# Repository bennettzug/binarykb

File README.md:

# binarykb
 
https://www.pcbway.com/project/shareproject/Two_Key_Keyboard.html

CURRENTLY BROKEN; DO NOT ORDER; MAY GET AROUND TO FIXING EVENTUALLY BUT IDK

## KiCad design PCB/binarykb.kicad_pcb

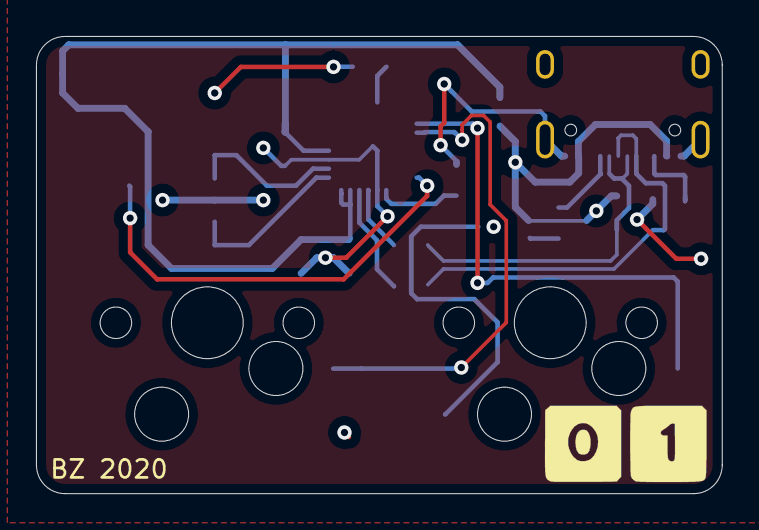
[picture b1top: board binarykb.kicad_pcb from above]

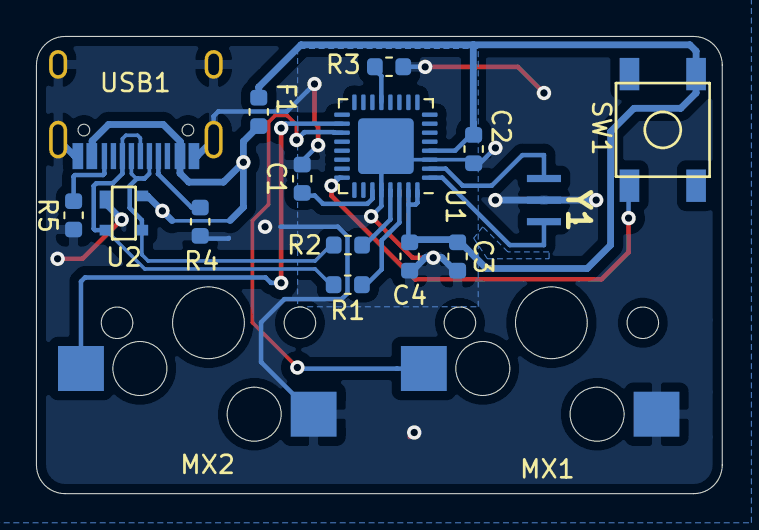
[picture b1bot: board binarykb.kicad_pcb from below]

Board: 2 copper layers, 38.1 x 25.4 mm, 17 parts (15 on the bottom side), 16 nets.

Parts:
C1: 1uF; C_0603_1608Metric
C2, C3: 0.1uF; C_0603_1608Metric
C4: 4.7uF; C_0603_1608Metric
F1: 500mA; Fuse_0603_1608Metric
MX1, MX2: MX-NoLED; MXOnly-1U-Hotswap
R1, R2: 22; R_0603_1608Metric
R3: 10k; R_0603_1608Metric
R4, R5: 5.1k; R_0603_1608Metric
SW1: SW_PUSH; SKQG-1155865
U1: ATmega32U2-MU; QFN-32-1EP_5x5mm_P0.5mm_EP3.1x3.1mm
U2: PRTR5V0U2X; SOT143B
USB1: HRO-TYPE-C-31-M-12
Y1: 16 MHz; CSTNE16M0V51Z000R0

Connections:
+5V: C2.1, C3.1, C4.1, F1.1, SW1.1, U1.4 (VCC), U1.31 (UVCC), U1.32 (AVCC)
D+: R2.2, U2.3 (IO2), USB1.5 (DN2), USB1.7 (DN1)
D-: R1.2, U2.2 (IO1), USB1.6 (DP1), USB1.8 (DP2)
GND: C1.2, C2.2, C3.2, C4.2, MX1.2 (ROW), MX2.2 (ROW), R3.1, R4.1, R5.1, U1.3 (GND), U1.28 (UGND), U1.33 (GND), U2.1 (GND), USB1.1 (GND), USB1.12 (GND), USB1.13 (SHIELD), Y1.2
MX1: MX1.1 (COL), U1.19 (PB5)
MX2: MX2.1 (COL), U1.18 (PB4)
unnamed: C1.1, U1.27 (UCAP)
unnamed: R1.1, U1.30 (D-)
unnamed: R2.1, U1.29 (D+)
unnamed: R3.2, U1.13 (~HWB/PD7)
unnamed: R4.2, USB1.4 (CC1)
unnamed: R5.2, USB1.10 (CC2)
unnamed: SW1.2, U1.24 (PC1/~RESET)
unnamed: U1.1 (XTAL1), Y1.1
unnamed: U1.2 (PC0/XTAL2), Y1.3
VCC: F1.2, U2.4 (VCC), USB1.2 (VBUS), USB1.11 (VBUS)

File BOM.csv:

Id,Designator,Package,Quantity,Designation
1,"R4,R5",R_0603_1608Metric,2,5.1k
2,R3,R_0603_1608Metric,1,10k
3,"R2,R1",R_0603_1608Metric,2,22k
4,F1,Fuse_0603_1608Metric,1,500mA
5,C4,C_0603_1608Metric,1,4.7uF
6,"C3,C2",C_0603_1608Metric,2,0.1uF
7,C1,C_0603_1608Metric,1,1uF
8,"MX1,MX2",MXOnly-1U-Hotswap,2,MX-NoLED
9,USB1,HRO-TYPE-C-31-M-12,1,HRO-TYPE-C-31-M-12
10,G***,binarykblogoFP,1,LOGO
11,SW1,SKQG-1155865,1,SW_PUSH
12,Y1,Resonator_SMD-3Pin_7.2x3.0mm,1,16 MHz
13,U2,SOT143B,1,PRTR5V0U2X
14,U1,QFN-32-1EP_5x5mm_P0.5mm_EP3.1x3.1mm,1,ATmega32U2-MU

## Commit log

2020-04-02 PCB Design
2020-04-02 changed the file system
2020-04-02 added the submodules (did it wrong but it should work?)
2020-04-03 Finalized PCB design + generated Gerbers
2020-04-16 redid gerbers
    probably some other things too
2020-04-16 added dimensions
2020-04-17 updated resonator
2020-04-17 fixed gerbers
2020-05-11 added case
2022-05-08 fixed values i think
2022-05-08 buncha things
2022-05-08 might as well
